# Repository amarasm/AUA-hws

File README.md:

# AUA-hws
This is merely for the homeworks of my university's programming course.

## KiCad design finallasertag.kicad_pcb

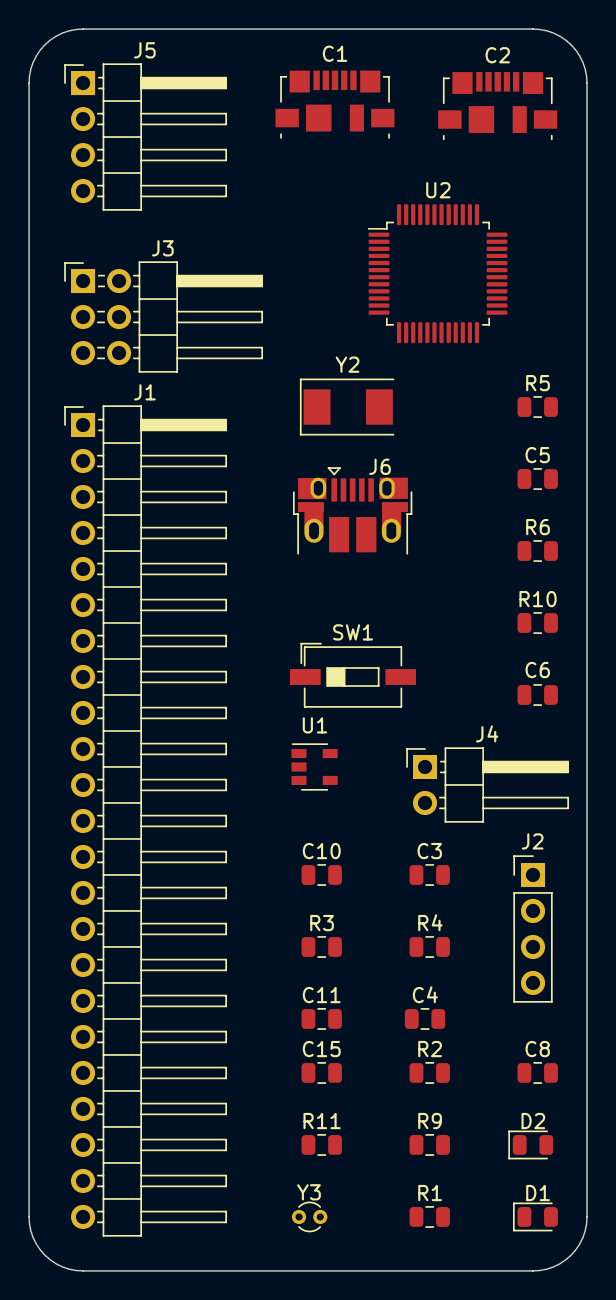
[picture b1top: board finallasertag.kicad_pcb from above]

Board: 2 copper layers, 39.4 x 87.6 mm, 32 parts (0 on the bottom side), 26 nets, no tracks yet.

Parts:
C1: 104,0603; USB_Micro-B_Molex_47346-0001
C2: 106,0603; USB_Micro-B_Molex_47346-0001
C3, C4, C8, C10, C11: 104,0603; C_0805_2012Metric
C5: 105,0805; C_0805_2012Metric
C6: 106,0805; C_0805_2012Metric
C15: 223,0603; C_0805_2012Metric
D1, D2: LED; LED_0805_2012Metric
J1: Conn_01x23_Male; PinHeader_1x23_P2.54mm_Horizontal
J2: 4P4C; PinHeader_1x04_P2.54mm_Vertical
J3: Conn_02x03_Odd_Even; PinHeader_2x03_P2.54mm_Horizontal
J4: 4P2C; PinHeader_1x02_P2.54mm_Horizontal
J5: Conn_01x04_Female; PinHeader_1x04_P2.54mm_Horizontal
J6: USB_B_Micro; USB_Micro-B_Amphenol_10103594-0001LF_Horizontal
R1, R5: 510R,0603; R_0805_2012Metric
R2: 10k,603; R_0805_2012Metric
R3, R4: 100K,0603; R_0805_2012Metric
R6: 1M; R_0805_2012Metric
R9, R11: 20R,0603; R_0805_2012Metric
R10: 4.7k,0603; R_0805_2012Metric
SW1: SW_Push; SW_DIP_SPSTx01_Slide_6.7x4.1mm_W6.73mm_P2.54mm_LowProfile_J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
U1: NCP1529A; SOT-23-5
U2: STM32F103C8Tx; LQFP-48_7x7mm_P0.5mm
Y2: 8MHz(C = 20p.0603); Crystal_SMD_0603-2Pin_6.0x3.5mm
Y3: 32.768K(C = 20p.0603); Crystal_Round_D1.0mm_Vertical

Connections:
+3V3: C6.1, C8.1, D1.2, D2.2, J3.1, J3.2, R2.1, U1.5
+5V: C5.1, J2.2, J4.2, J6.1, R10.1, R10.2, R11.2, U1.1, U1.3, U2.12
GNDREF: C1.2, C2.2, C3.2, C4.2, C5.2, C6.2, C8.2, C10.2, C11.2, C15.2, J2.1, J3.5, J3.6, J4.1, J5.4, J6.4, J6.5, R1.1, SW1.2, U1.2, U2.8, U2.23, U2.35, U2.47, Y2.2, Y3.2
unnamed: C1.1, J5.1
unnamed: C2.1, R2.2, SW1.1, U2.7
unnamed: C3.1, U2.9
unnamed: C4.1, U2.48
unnamed: C10.1, U2.36
unnamed: C11.1, U2.24
unnamed: C15.1, U1.4
unnamed: D1.1, R1.2
unnamed: D2.1, R5.2
unnamed: J2.4, U2.42
unnamed: J3.3, R4.2
unnamed: J3.4, R3.1
unnamed: J5.2, U2.34
unnamed: J5.3, U2.37
unnamed: J6.2, R9.1
unnamed: J6.3, R11.1
unnamed: R3.2, U2.20
unnamed: R4.1, U2.44
unnamed: R5.1, U2.2
unnamed: R6.1, U2.5, Y2.1
unnamed: R6.2, U2.6
unnamed: R9.2, U2.11
unnamed: U2.14, Y3.1

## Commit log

2019-09-12 Create Schedule
2019-09-17 Create Rooms(Classrooms and offices)
2019-10-27 (Couldn't upload it using the git thingy)
    I couldn't find the git I guess something's wrong!
